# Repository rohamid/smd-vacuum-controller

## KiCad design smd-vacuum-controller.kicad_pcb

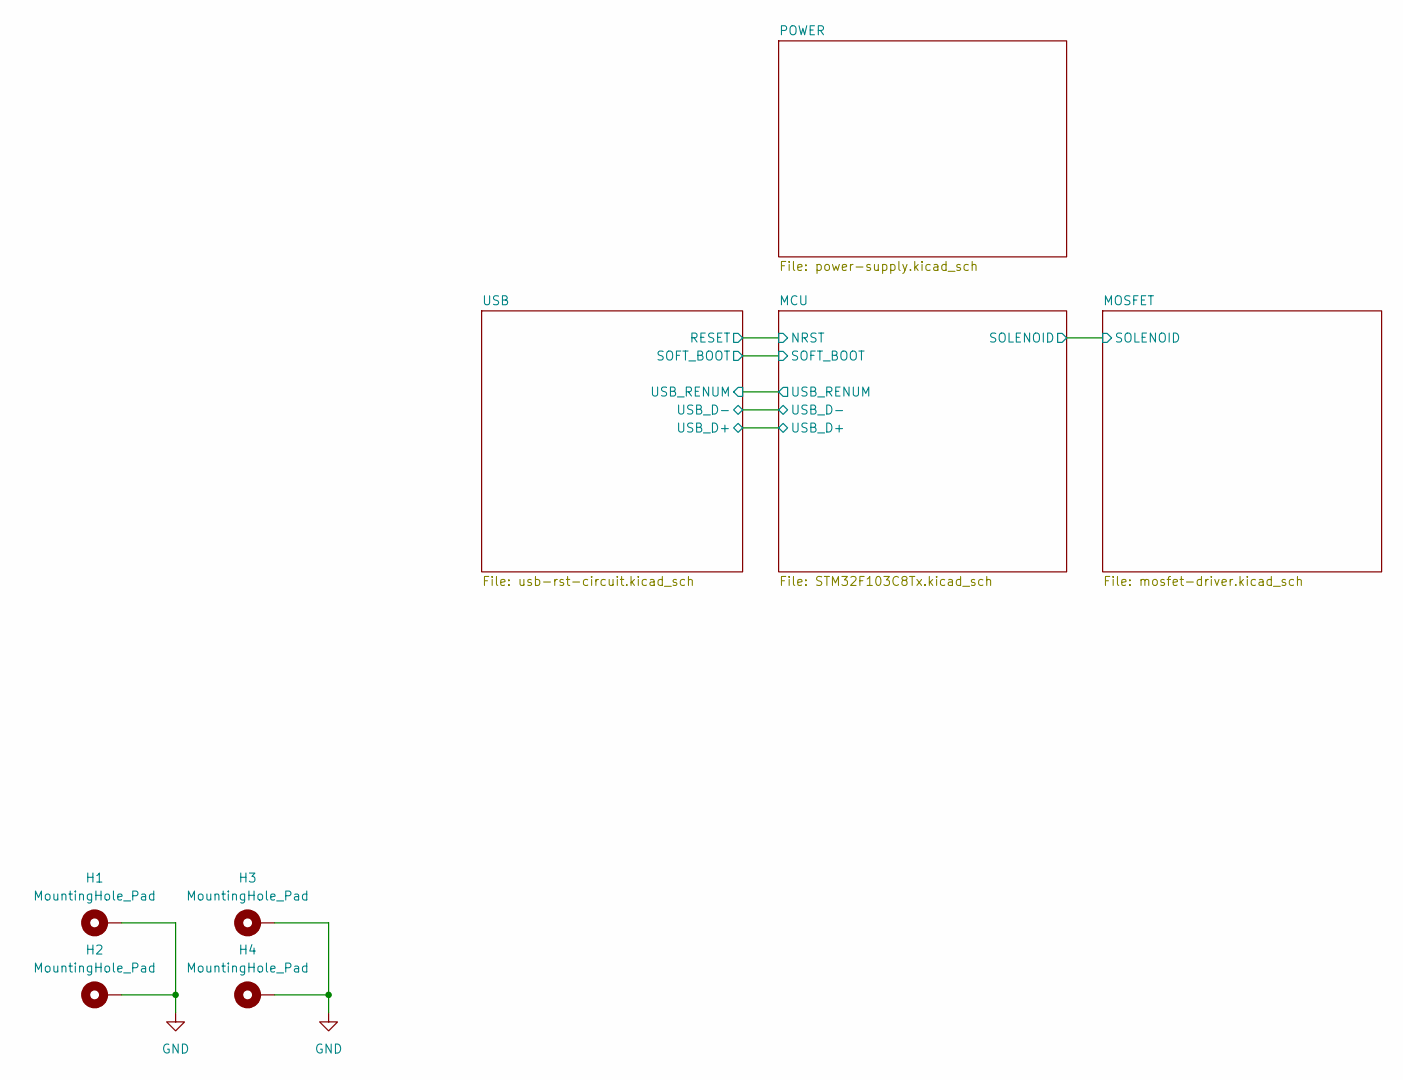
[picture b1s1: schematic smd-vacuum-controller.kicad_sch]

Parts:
H1, H2, H3, H4: MountingHole_Pad; MountingHole_3.2mm_M3_Pad_Via

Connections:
GND: H1.1, H2.1, H3.1, H4.1; also elsewhere on the board

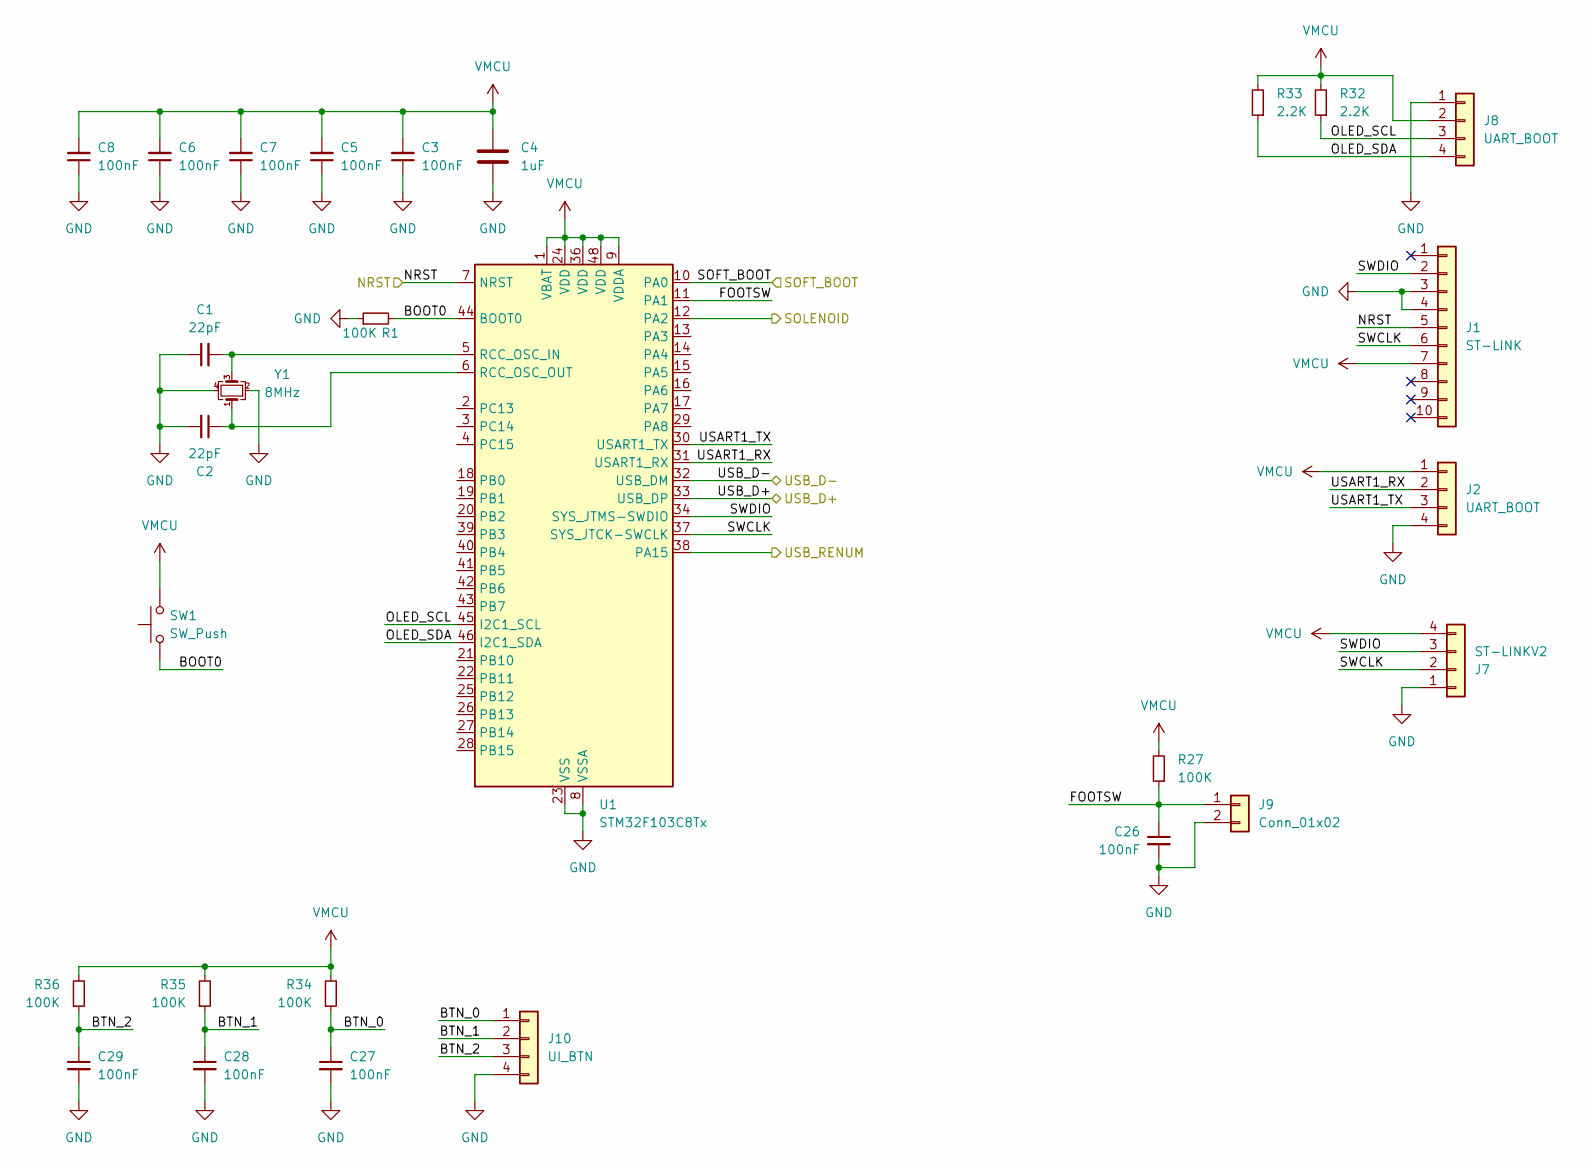
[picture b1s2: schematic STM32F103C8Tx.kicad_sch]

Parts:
C1, C2: 22pF; C_0603_1608Metric
C3, C5, C6, C7, C8, C26, C27, C28, C29: 100nF; C_0603_1608Metric
C4: 1uF; C_0805_2012Metric
J1: ST-LINK; Tag-Connect_TC2050-IDC-NL_2x05_P1.27mm_Vertical
J2, J8: UART_BOOT; JST_PH_B4B-PH-K_1x04_P2.00mm_Vertical
J7: ST-LINKV2; JST_PH_B4B-PH-K_1x04_P2.00mm_Vertical
J9: Conn_01x02; JST_PH_B2B-PH-K_1x02_P2.00mm_Vertical
J10: UI_BTN; JST_PH_B4B-PH-K_1x04_P2.00mm_Vertical
R1, R27, R34, R35, R36: 100K; R_0603_1608Metric
R32, R33: 2.2K; R_0603_1608Metric
SW1: SW_Push; SW_PUSH_6mm_H5mm
U1: STM32F103C8Tx; LQFP-48_7x7mm_P0.5mm
Y1: 8MHz; Crystal_SMD_3225-4Pin_3.2x2.5mm

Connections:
/MCU/BOOT0: R1.2, SW1.1, U1.44 (BOOT0)
/MCU/BTN_0: C27.1, J10.1, R34.1
/MCU/BTN_1: C28.1, J10.2, R35.1
/MCU/BTN_2: C29.1, J10.3, R36.1
/MCU/FOOTSW: C26.1, J9.1, R27.1, U1.11 (PA1)
/MCU/NRST: J1.5, U1.7 (NRST); also elsewhere on the board
/MCU/OLED_SCL: J8.3, R32.1, U1.45 (I2C1_SCL)
/MCU/OLED_SDA: J8.4, R33.1, U1.46 (I2C1_SDA)
/MCU/SOFT_BOOT: U1.10 (PA0); also elsewhere on the board
/MCU/SWCLK: J1.6, J7.2, U1.37 (SYS_JTCK-SWCLK)
/MCU/SWDIO: J1.2, J7.3, U1.34 (SYS_JTMS-SWDIO)
/MCU/USART1_RX: J2.2, U1.31 (USART1_RX)
/MCU/USART1_TX: J2.3, U1.30 (USART1_TX)
/MCU/USB_D+: U1.33 (USB_DP); also elsewhere on the board
/MCU/USB_D-: U1.32 (USB_DM); also elsewhere on the board
/MOSFET/SOLENOID: U1.12 (PA2); also elsewhere on the board
/USB/USB_RENUM: U1.38 (PA15); also elsewhere on the board
GND: C1.1, C2.2, C3.1, C4.2, C5.1, C6.1, C7.1, C8.1, C26.2, C27.2, C28.2, C29.2, J1.3, J1.4, J2.4, J7.1, J8.1, J9.2, J10.4, R1.1, U1.8 (VSSA), U1.23 (VSS), U1.35 (VSS), U1.47 (VSS), Y1.2, Y1.4; also elsewhere on the board
unnamed: C1.2, U1.5 (RCC_OSC_IN), Y1.3
unnamed: C2.1, U1.6 (RCC_OSC_OUT), Y1.1
VMCU: C3.2, C4.1, C5.2, C6.2, C7.2, C8.2, J1.7, J2.1, J7.4, J8.2, R27.2, R32.2, R33.2, R34.2, R35.2, R36.2, SW1.2, U1.1 (VBAT), U1.9 (VDDA), U1.24 (VDD), U1.36 (VDD), U1.48 (VDD); also elsewhere on the board

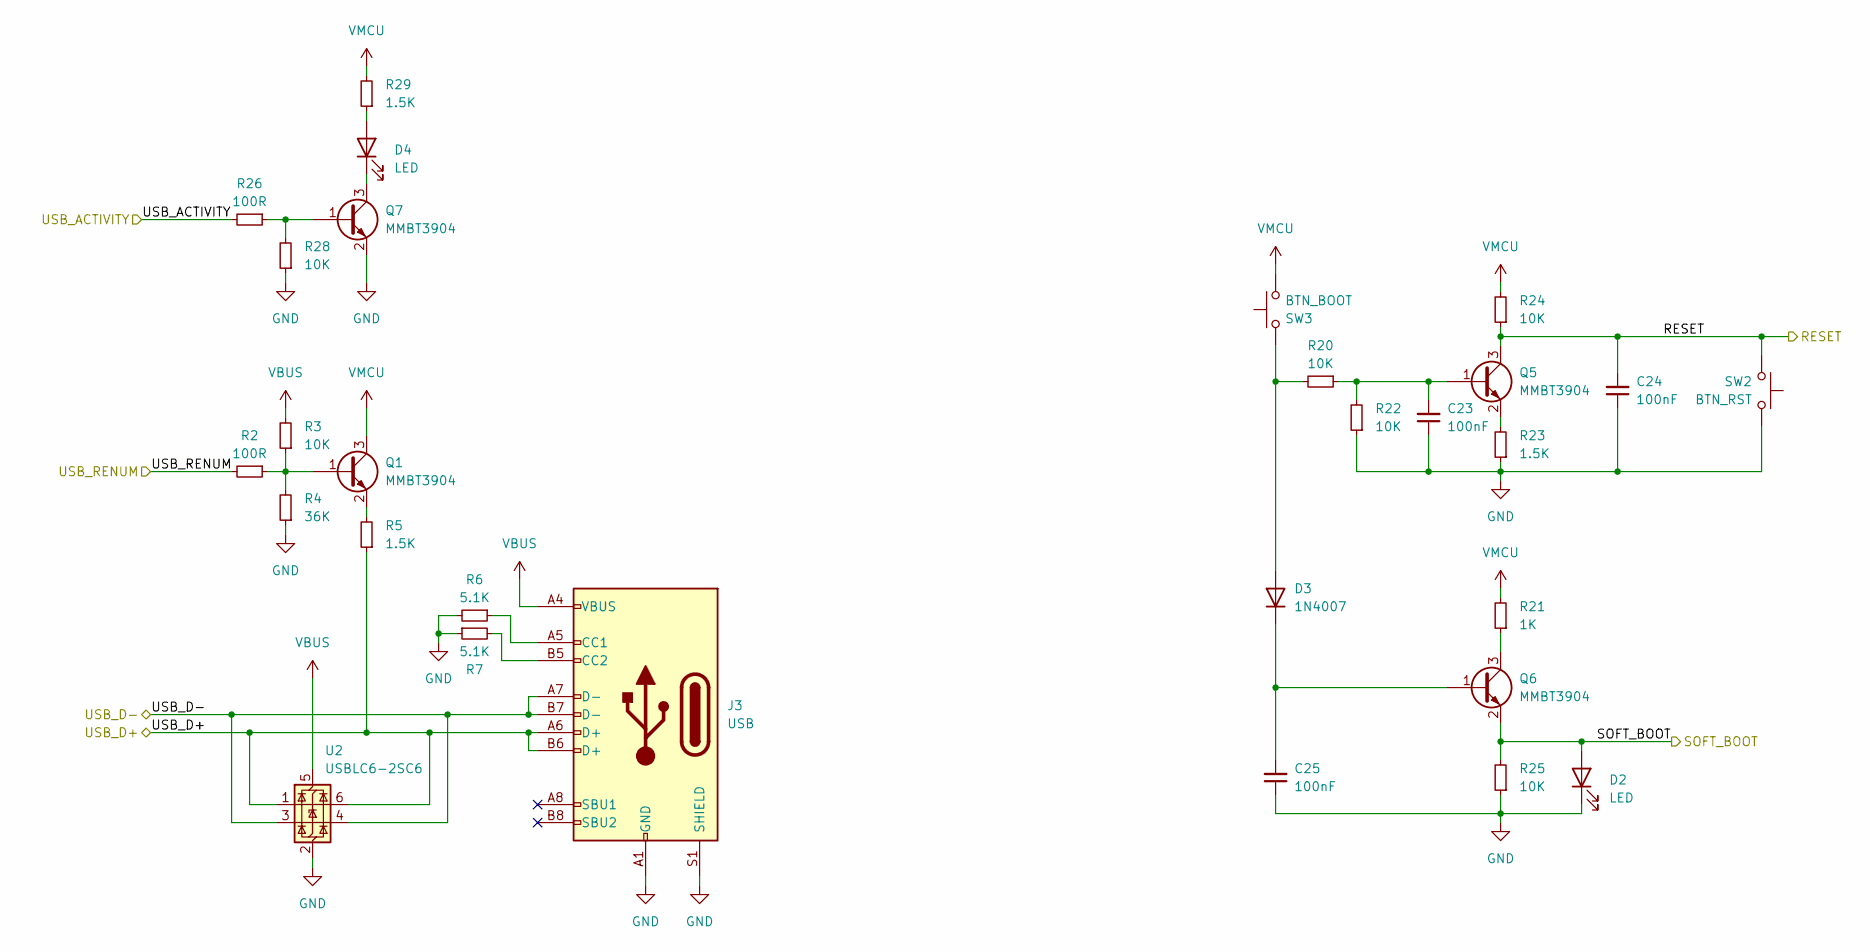
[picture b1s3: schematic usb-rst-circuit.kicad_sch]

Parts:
C23, C24, C25: 100nF; C_0603_1608Metric
D2: LED; LED_0805_2012Metric
D3: 1N4007; D_SOD-123F
D4: LED; LED_D3.0mm_Horizontal_O1.27mm_Z2.0mm
J3: USB; USB_C_Receptacle_G-Switch_GT-USB-7010ASV
Q1, Q5, Q6, Q7: MMBT3904; SOT-23
R2, R26: 100R; R_0603_1608Metric
R3, R20, R22, R24, R25, R28: 10K; R_0603_1608Metric
R4: 36K; R_0603_1608Metric
R5, R23, R29: 1.5K; R_0603_1608Metric
R6, R7: 5.1K; R_0603_1608Metric
R21: 1K; R_0603_1608Metric
SW2: BTN_RST; SW_PUSH_6mm_H5mm
SW3: BTN_BOOT; SW_Tactile_SPST_Angled_PTS645Vx83-2LFS
U2: USBLC6-2SC6; SOT-23-6

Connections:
/MCU/NRST: C24.2, Q5.3 (C), R24.1, SW2.2; also elsewhere on the board
/MCU/SOFT_BOOT: D2.2 (A), Q6.2 (E), R25.2; also elsewhere on the board
/MCU/USB_D+: J3.A6 (D+), J3.B6 (D+), R5.1, U2.1 (I/O1), U2.6 (I/O1); also elsewhere on the board
/MCU/USB_D-: J3.A7 (D-), J3.B7 (D-), U2.3 (I/O2), U2.4 (I/O2); also elsewhere on the board
/USB/USB_ACTIVITY: R26.2
/USB/USB_RENUM: R2.2; also elsewhere on the board
GND: C23.1, C24.1, C25.1, D2.1 (K), J3.A1 (GND), J3.A12 (GND), J3.B1 (GND), J3.B12 (GND), J3.S1 (SHIELD), Q7.2 (E), R4.1, R6.2, R7.1, R22.1, R23.1, R25.1, R28.1, SW2.1, U2.2 (GND); also elsewhere on the board
unnamed: D3.2 (A), R20.2, SW3.2
unnamed: C25.2, D3.1 (K), Q6.1 (B)
unnamed: D4.2 (A), R29.1
unnamed: D4.1 (K), Q7.3 (C)
unnamed: J3.A5 (CC1), R6.1
unnamed: J3.B5 (CC2), R7.2
unnamed: Q1.1 (B), R2.1, R3.1, R4.2
unnamed: Q1.2 (E), R5.2
unnamed: C23.2, Q5.1 (B), R20.1, R22.2
unnamed: Q5.2 (E), R23.2
unnamed: Q6.3 (C), R21.1
unnamed: Q7.1 (B), R26.1, R28.2
VBUS: J3.A4 (VBUS), J3.A9 (VBUS), J3.B4 (VBUS), J3.B9 (VBUS), R3.2, U2.5 (VBUS)
VMCU: Q1.3 (C), R21.2, R24.2, R29.2, SW3.1; also elsewhere on the board

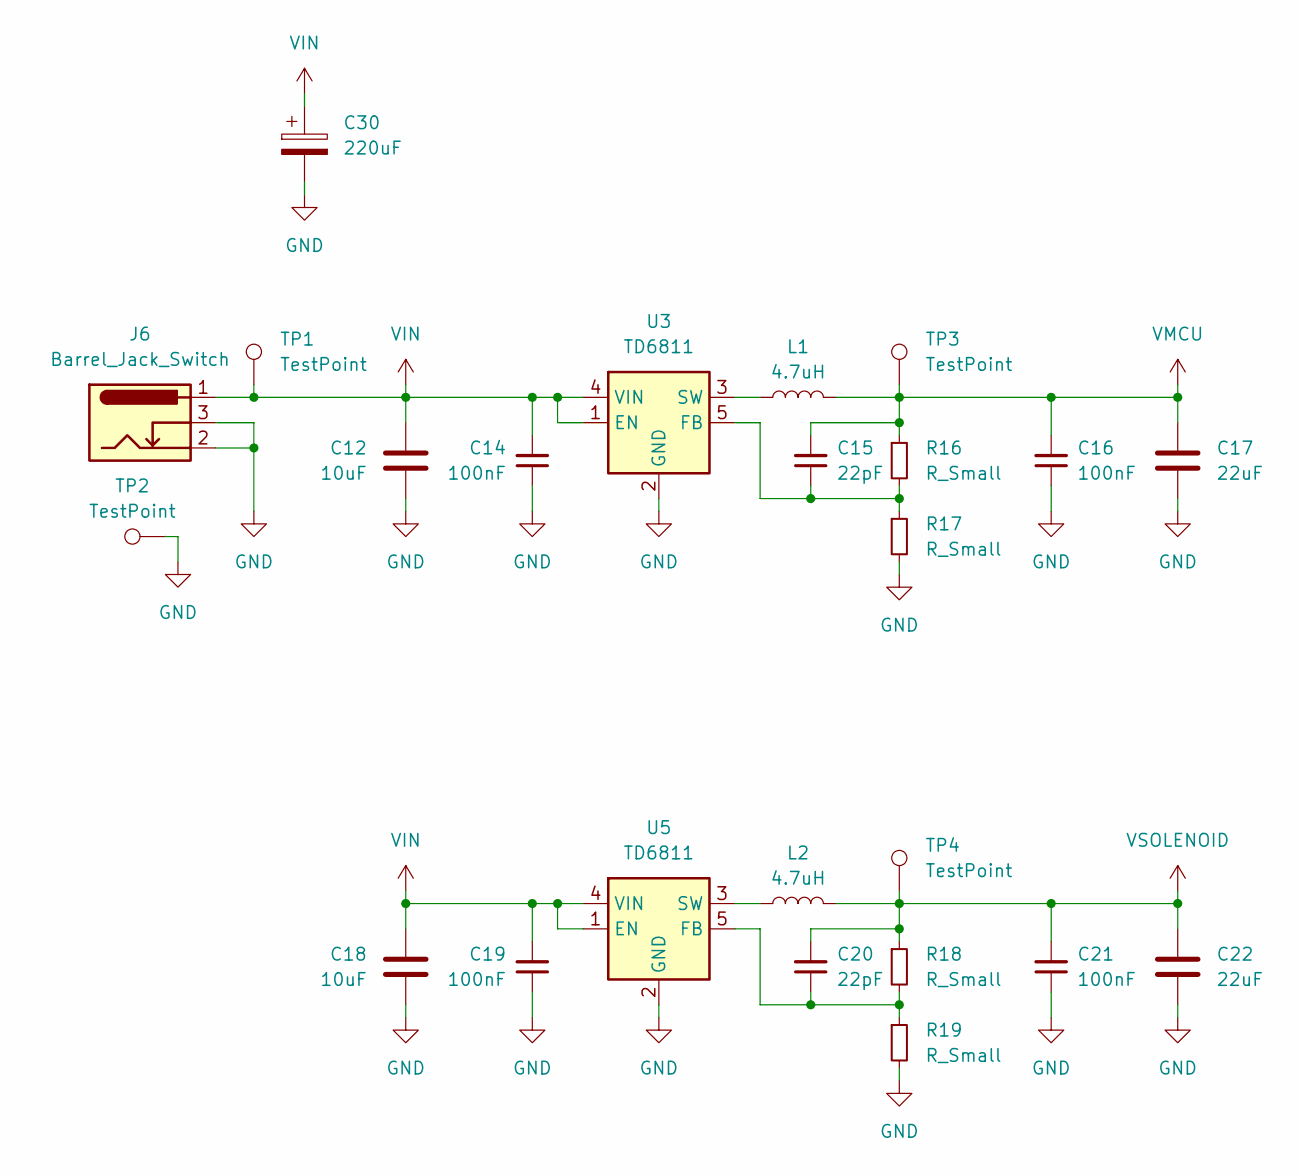
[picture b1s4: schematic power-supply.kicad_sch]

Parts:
C12, C18: 10uF; C_0805_2012Metric
C14, C16, C19, C21: 100nF; C_0603_1608Metric
C15, C20: 22pF; C_0603_1608Metric
C17, C22: 22uF; C_0805_2012Metric
C30: 220uF; CP_Radial_D6.3mm_P2.50mm
J6: Barrel_Jack_Switch; BarrelJack_Horizontal
L1, L2: 4.7uH; L_Abracon_ASPI-0425
R16, R17, R18, R19: R_Small; R_0603_1608Metric
TP1, TP2, TP3, TP4: TestPoint; TestPoint_Pad_D1.0mm
U3, U5: TD6811; SOT-23-5

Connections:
GND: C12.2, C14.1, C16.1, C17.2, C18.2, C19.1, C21.1, C22.2, C30.2, J6.2, J6.3, R17.2, R19.2, TP2.1, U3.2 (GND), U5.2 (GND); also elsewhere on the board
unnamed: C15.1, R16.2, R17.1, U3.5 (FB)
unnamed: L1.1, U3.3 (SW)
unnamed: C20.1, R18.2, R19.1, U5.5 (FB)
unnamed: L2.1, U5.3 (SW)
VIN: C12.1, C14.2, C18.1, C19.2, C30.1, J6.1, TP1.1, U3.1 (EN), U3.4 (VIN), U5.1 (EN), U5.4 (VIN)
VMCU: C15.2, C16.2, C17.1, L1.2, R16.1, TP3.1; also elsewhere on the board
VSOLENOID: C20.2, C21.2, C22.1, L2.2, R18.1, TP4.1; also elsewhere on the board

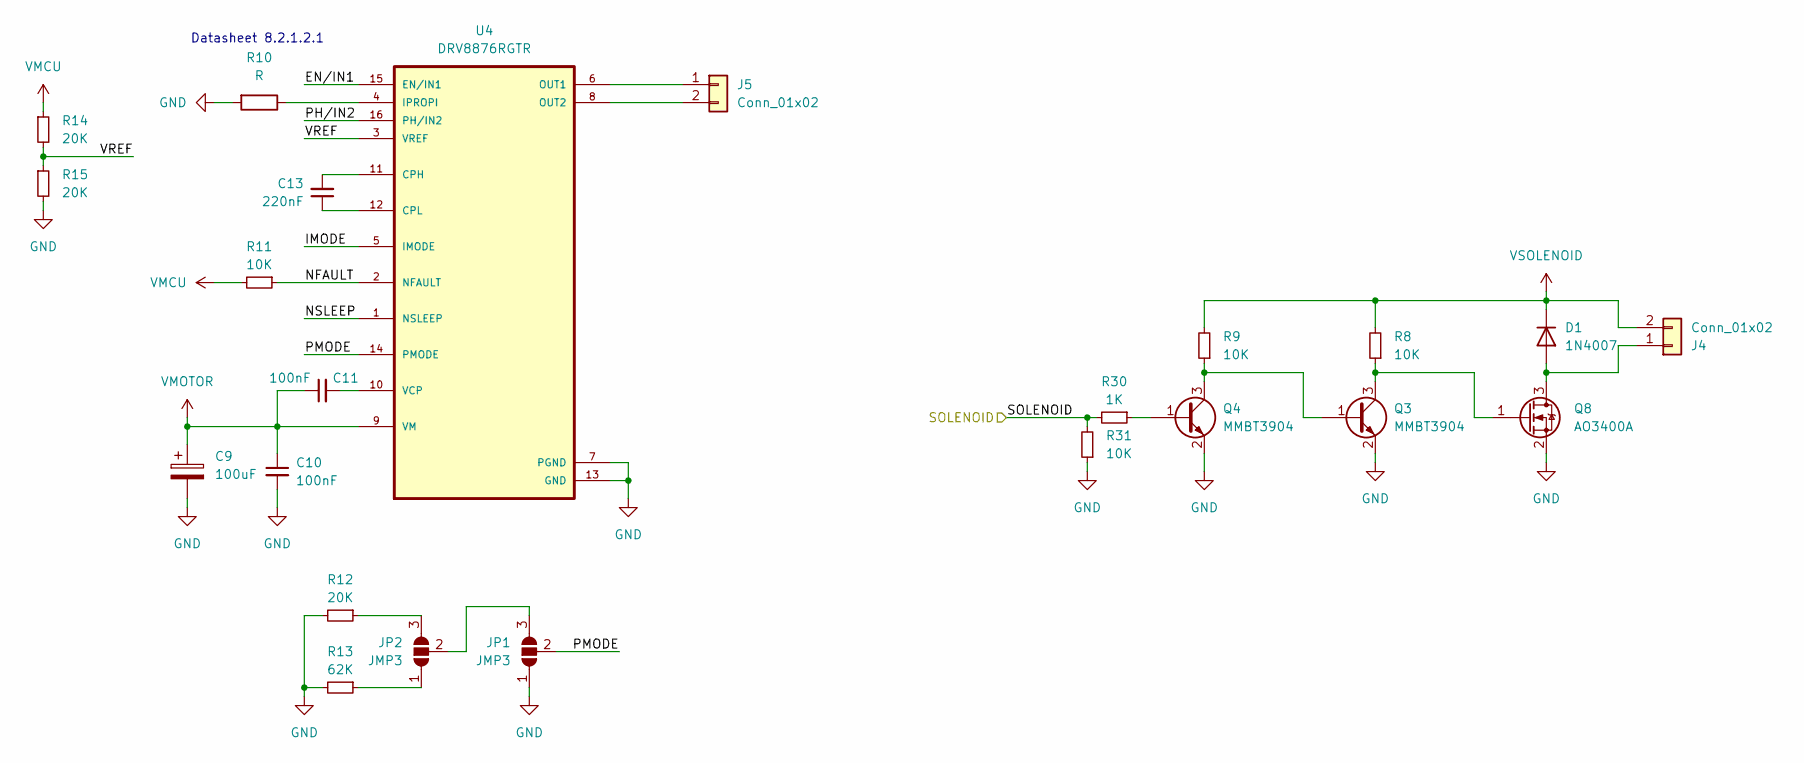
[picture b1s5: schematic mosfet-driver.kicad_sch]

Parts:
C9: 100uF; CP_Radial_D6.3mm_P2.50mm
C10, C11: 100nF; C_0603_1608Metric
C13: 220nF; C_0603_1608Metric
D1: 1N4007; D_SOD-123F
J4, J5: Conn_01x02; JST_PH_B2B-PH-K_1x02_P2.00mm_Vertical
JP1, JP2: JMP3; SolderJumper-3_P1.3mm_Open_Pad1.0x1.5mm
Q3, Q4: MMBT3904; SOT-23
Q8: AO3400A; SOT-23
R8, R9, R11, R31: 10K; R_0603_1608Metric
R10: R; R_0603_1608Metric
R12, R14, R15: 20K; R_0603_1608Metric
R13: 62K; R_0603_1608Metric
R30: 1K; R_0603_1608Metric
U4: DRV8876RGTR

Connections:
/MOSFET/EN/IN1: U4.15 (EN/IN1)
/MOSFET/IMODE: U4.5 (IMODE)
/MOSFET/NFAULT: R11.1, U4.2 (NFAULT)
/MOSFET/NSLEEP: U4.1 (NSLEEP)
/MOSFET/PH/IN2: U4.16 (PH/IN2)
/MOSFET/PMODE: JP1.2 (C), U4.14 (PMODE)
/MOSFET/SOLENOID: R30.2, R31.2; also elsewhere on the board
/MOSFET/VREF: R14.2, R15.1, U4.3 (VREF)
GND: C9.2, C10.2, JP1.1 (A), Q3.2 (E), Q4.2 (E), Q8.2 (S), R10.2, R12.2, R13.2, R15.2, R31.1, U4.7 (PGND), U4.13 (GND); also elsewhere on the board
unnamed: D1.2 (A), J4.1, Q8.3 (D)
unnamed: J5.1, U4.6 (OUT1)
unnamed: J5.2, U4.8 (OUT2)
unnamed: JP1.3 (B), JP2.2 (C)
unnamed: JP2.1 (A), R13.1
unnamed: JP2.3 (B), R12.1
unnamed: Q3.1 (B), Q4.3 (C), R9.1
unnamed: Q3.3 (C), Q8.1 (G), R8.1
unnamed: Q4.1 (B), R30.1
unnamed: C13.2, U4.11 (CPH)
unnamed: C13.1, U4.12 (CPL)
unnamed: R10.1, U4.4 (IPROPI)
unnamed: C11.2, U4.10 (VCP)
VMCU: R11.2, R14.1; also elsewhere on the board
VMOTOR: C9.1, C10.1, C11.1, U4.9 (VM)
VSOLENOID: D1.1 (K), J4.2, R8.2, R9.2; also elsewhere on the board

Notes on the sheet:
Datasheet 8.2.1.2.1

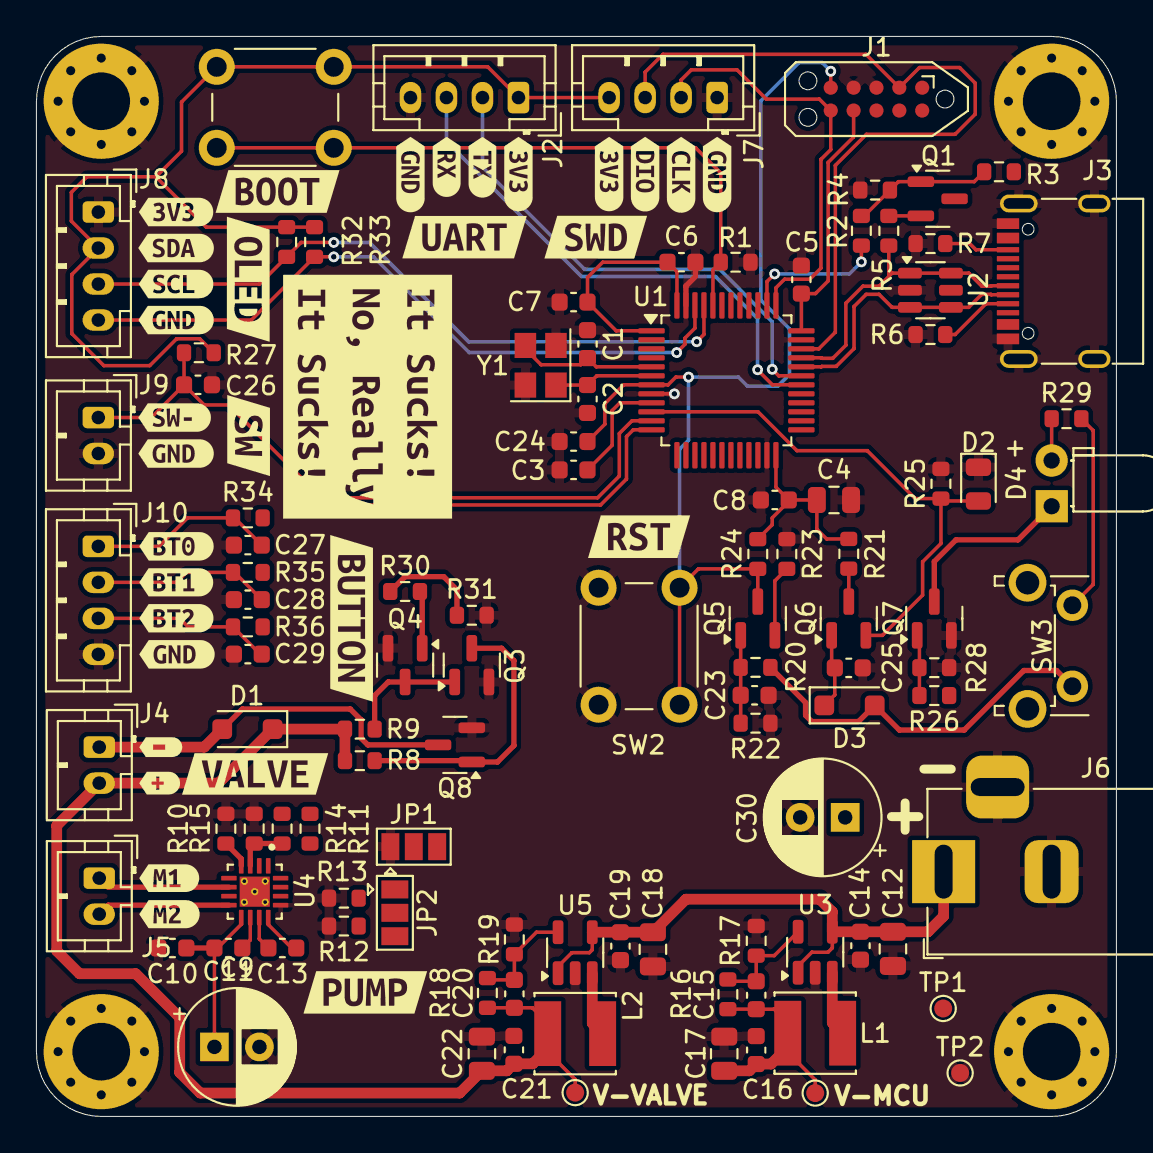
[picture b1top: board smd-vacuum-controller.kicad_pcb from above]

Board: 2 copper layers, 60.0 x 60.0 mm, 140 parts (0 on the bottom side), 57 nets.

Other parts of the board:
kibuzzard-68A6E7A0: G***; kibuzzard-68A6E7A0
kibuzzard-68A6E7E9: G***; kibuzzard-68A6E7E9
kibuzzard-68A6E8E7: G***; kibuzzard-68A6E8E7
kibuzzard-68A6E8EF: G***; kibuzzard-68A6E8EF
kibuzzard-68A6E83D: G***; kibuzzard-68A6E83D
kibuzzard-68A6E781: G***; kibuzzard-68A6E781
kibuzzard-68A6E791, kibuzzard-68A6E791#2, kibuzzard-68A6E791#3: G***; kibuzzard-68A6E791
kibuzzard-68A6E799, kibuzzard-68A6E799#2, kibuzzard-68A6E799#3, kibuzzard-68A6E799#4, kibuzzard-68A6E799#5: G***; kibuzzard-68A6E799
kibuzzard-68A6E857: G***; kibuzzard-68A6E857
kibuzzard-68A6ED99: G***; kibuzzard-68A6ED99
kibuzzard-68A7C63E: G***; kibuzzard-68A7C63E
kibuzzard-68A7C639: G***; kibuzzard-68A7C639
kibuzzard-68A7C770: G***; kibuzzard-68A7C770
kibuzzard-68A7C776: G***; kibuzzard-68A7C776
kibuzzard-68AA9AC7: G***; kibuzzard-68AA9AC7
kibuzzard-68AA9ACD: G***; kibuzzard-68AA9ACD
kibuzzard-68AA9AD3: G***; kibuzzard-68AA9AD3
kibuzzard-68AA9F3B: G***; kibuzzard-68AA9F3B
kibuzzard-68AA9F3F: G***; kibuzzard-68AA9F3F
kibuzzard-68AA9F5E: G***; kibuzzard-68AA9F5E
kibuzzard-68AA9F08: G***; kibuzzard-68AA9F08
kibuzzard-68AA9F21: G***; kibuzzard-68AA9F21
kibuzzard-68AA9F28: G***; kibuzzard-68AA9F28
kibuzzard-68AA9F46: G***; kibuzzard-68AA9F46
kibuzzard-68AA9F51: G***; kibuzzard-68AA9F51
kibuzzard-68AA9F57: G***; kibuzzard-68AA9F57

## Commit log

2025-08-21 Added footwitch, usb led activity
2025-08-22 layouting Power, Motor section
2025-08-24 Added push button connector
